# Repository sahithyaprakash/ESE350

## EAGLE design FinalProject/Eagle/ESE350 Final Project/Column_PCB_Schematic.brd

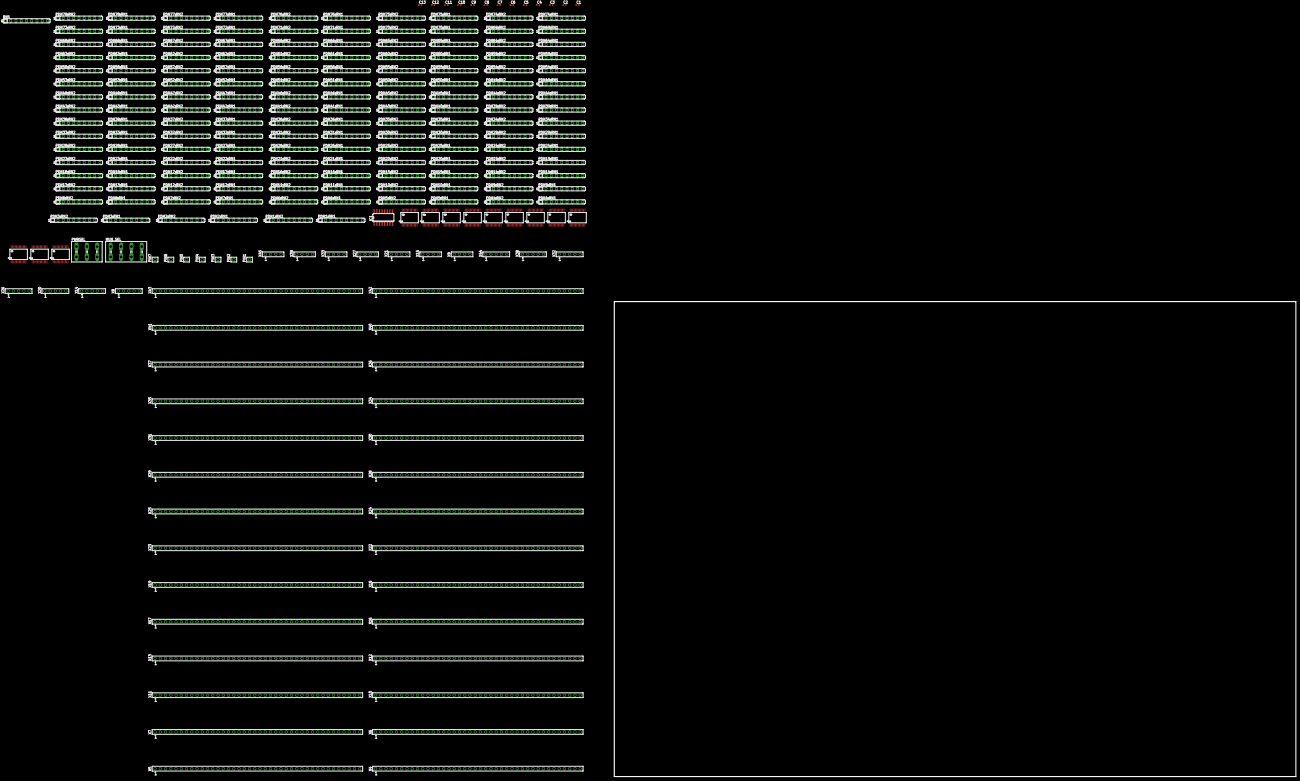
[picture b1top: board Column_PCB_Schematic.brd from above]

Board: 2 copper layers, 329.9 x 229.9 mm, 234 parts (0 on the bottom side), 1229 nets, no tracks yet.

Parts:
C1, C2, C3, C4, C5, C6, C7, C8, C9, C10, C11, C12, C13: 0.1uF; C0402
IC1: 74AC11238D; SO16
MUX_SEL: SH5-4
PDN1:RN1, PDN1:RN2, PDN2:RN1, PDN2:RN2, PDN3:RN1, PDN3:RN2, PDN4:RN1, PDN4:RN2, PDN5:RN1, PDN5:RN2, PDN6:RN1, PDN6:RN2, PDN7:RN1, PDN7:RN2, PDN8:RN1, PDN8:RN2, PDN9:RN1, PDN9:RN2, PDN10:RN1, PDN10:RN2, PDN11:RN1, PDN11:RN2, PDN12:RN1, PDN12:RN2, PDN13:RN1, PDN13:RN2, PDN14:RN1, PDN14:RN2, PDN15:RN1, PDN15:RN2, PDN16:RN1, PDN16:RN2, PDN17:RN1, PDN17:RN2, PDN18:RN1, PDN18:RN2, PDN19:RN1, PDN19:RN2, PDN20:RN1, PDN20:RN2, PDN21:RN1, PDN21:RN2, PDN22:RN1, PDN22:RN2, PDN23:RN1, PDN23:RN2, PDN24:RN1, PDN24:RN2, PDN25:RN1, PDN25:RN2, PDN26:RN1, PDN26:RN2, PDN27:RN1, PDN27:RN2, PDN28:RN1, PDN28:RN2, PDN29:RN1, PDN29:RN2, PDN30:RN1, PDN30:RN2, PDN31:RN1, PDN31:RN2, PDN32:RN1, PDN32:RN2, PDN33:RN1, PDN33:RN2, PDN34:RN1, PDN34:RN2, PDN35:RN1, PDN35:RN2, PDN36:RN1, PDN36:RN2, PDN37:RN1, PDN37:RN2, PDN38:RN1, PDN38:RN2, PDN39:RN1, PDN39:RN2, PDN40:RN1, PDN40:RN2, PDN41:RN1, PDN41:RN2, PDN42:RN1, PDN42:RN2, PDN43:RN1, PDN43:RN2, PDN44:RN1, PDN44:RN2, PDN45:RN1, PDN45:RN2, PDN46:RN1, PDN46:RN2, PDN47:RN1, PDN47:RN2, PDN48:RN1, PDN48:RN2, PDN49:RN1, PDN49:RN2, PDN50:RN1, PDN50:RN2, PDN51:RN1, PDN51:RN2, PDN52:RN1, PDN52:RN2, PDN53:RN1, PDN53:RN2, PDN54:RN1, PDN54:RN2, PDN55:RN1, PDN55:RN2, PDN56:RN1, PDN56:RN2, PDN57:RN1, PDN57:RN2, PDN58:RN1, PDN58:RN2, PDN59:RN1, PDN59:RN2, PDN60:RN1, PDN60:RN2, PDN61:RN1, PDN61:RN2, PDN62:RN1, PDN62:RN2, PDN63:RN1, PDN63:RN2, PDN64:RN1, PDN64:RN2, PDN65:RN1, PDN65:RN2, PDN66:RN1, PDN66:RN2, PDN67:RN1, PDN67:RN2, PDN68:RN1, PDN68:RN2, PDN69:RN1, PDN69:RN2, PDN70:RN1, PDN70:RN2, PDN71:RN1, PDN71:RN2, PDN72:RN1, PDN72:RN2, PDN73:RN1, PDN73:RN2, PDN74:RN1, PDN74:RN2, PDN75:RN1, PDN75:RN2, PDN76:RN1, PDN76:RN2, PDN77:RN1, PDN77:RN2, PDN78:RN1, PDN78:RN2: 560K; SIL9
PIN1, PIN2, PIN3, PIN4, PIN5, PIN6, PIN7: SSW-101-02-S-S
PWRSEL: SH5-3
RN1: 560K; SIL9
U$1, U$2, U$3, U$4, U$5, U$6, U$7, U$8, U$9, U$10, U$11, U$12: MUX-74HC4067SMD; SSOP24
X4, X5, X6, X7, X10, X11, X12, X13, X16, X17, X18, X19, X22, X23, X24, X25, X28, X29, X30, X31, X34, X35, X36, X37, X40, X41, X42, X43: SSW-140-02-S-S
X8, X14, X20, X26, X32, X38, X44: SSW-105-02-S-S
X9, X15, X21, X27, X33, X39, X45: SSW-104-02-S-S

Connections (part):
GND: IC1.4, IC1.9, IC1.10, PDN1:RN1.1, PDN1:RN2.1, PDN2:RN1.1, PDN2:RN2.1, PDN3:RN1.1, PDN3:RN2.1, PDN4:RN1.1, PDN4:RN2.1, PDN5:RN1.1, PDN5:RN2.1, PDN6:RN1.1, PDN6:RN2.1, PDN7:RN1.1, PDN7:RN2.1, PDN8:RN1.1, PDN8:RN2.1, PDN9:RN1.1, PDN9:RN2.1, PDN10:RN1.1, PDN10:RN2.1, PDN11:RN1.1, PDN11:RN2.1, PDN12:RN1.1, PDN12:RN2.1, PDN13:RN1.1, PDN13:RN2.1, PDN14:RN1.1, PDN14:RN2.1, PDN15:RN1.1, PDN15:RN2.1, PDN16:RN1.1, PDN16:RN2.1, PDN17:RN1.1, PDN17:RN2.1, PDN18:RN1.1, PDN18:RN2.1, PDN19:RN1.1, PDN19:RN2.1, PDN20:RN1.1, PDN20:RN2.1, PDN21:RN1.1, PDN21:RN2.1, PDN22:RN1.1, PDN22:RN2.1, PDN23:RN1.1, PDN23:RN2.1, PDN24:RN1.1, PDN24:RN2.1, PDN25:RN1.1, PDN25:RN2.1, PDN26:RN1.1, PDN26:RN2.1, PDN27:RN1.1, PDN27:RN2.1, PDN28:RN1.1, PDN28:RN2.1, PDN29:RN1.1, PDN29:RN2.1, PDN30:RN1.1, PDN30:RN2.1, PDN31:RN1.1, PDN31:RN2.1, PDN32:RN1.1, PDN32:RN2.1, PDN33:RN1.1, PDN33:RN2.1, PDN34:RN1.1, PDN34:RN2.1, PDN35:RN1.1, PDN35:RN2.1, PDN36:RN1.1, PDN36:RN2.1, PDN37:RN1.1, PDN37:RN2.1, PDN38:RN1.1, PDN38:RN2.1, PDN39:RN1.1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
L1S0: MUX_SEL.8, U$1.10, U$2.10, U$3.10, U$4.10, U$5.10, U$6.10, U$7.10, U$8.10, U$9.10, U$10.10, U$11.10
L1S1: MUX_SEL.7, U$1.11, U$2.11, U$3.11, U$4.11, U$5.11, U$6.11, U$7.11, U$8.11, U$9.11, U$10.11, U$11.11
L1S2: MUX_SEL.6, U$1.14, U$2.14, U$3.14, U$4.14, U$5.14, U$6.14, U$7.14, U$8.14, U$9.14, U$10.14, U$11.14
L1S3: MUX_SEL.5, U$1.13, U$2.13, U$3.13, U$4.13, U$5.13, U$6.13, U$7.13, U$8.13, U$9.13, U$10.13, U$11.13
L2S0: MUX_SEL.4, U$12.10
L2S1: MUX_SEL.3, U$12.11
L2S2: MUX_SEL.2, U$12.14
L2S3: MUX_SEL.1, U$12.13
unnamed: PDN78:RN2.7, U$11.1
unnamed: PDN78:RN2.8, U$2.1
unnamed: PDN78:RN2.9, U$6.1
unnamed: PDN78:RN1.2, U$5.1
unnamed: PDN78:RN1.3, U$4.1
unnamed: PDN78:RN1.4, U$3.1
unnamed: PDN78:RN1.6, U$7.1
unnamed: PDN78:RN1.7, U$8.1
unnamed: PDN78:RN1.8, U$9.1
unnamed: PDN78:RN1.9, U$10.1
unnamed: PDN1:RN1.9, X4.1
unnamed: PDN1:RN1.7, X4.2
unnamed: PDN1:RN1.5, X4.3
unnamed: PDN1:RN1.3, X4.4
unnamed: PDN1:RN2.9, X4.5
unnamed: PDN1:RN2.7, X4.6
unnamed: PDN1:RN2.5, X4.7
unnamed: PDN1:RN2.3, X4.8
unnamed: PDN2:RN1.9, X4.9
unnamed: PDN2:RN1.7, X4.10
unnamed: PDN2:RN1.5, X4.11
unnamed: PDN2:RN1.3, X4.12
unnamed: PDN2:RN2.9, X4.13
unnamed: PDN2:RN2.7, X4.14
unnamed: PDN2:RN2.5, X4.15
unnamed: PDN2:RN2.3, X4.16
unnamed: PDN3:RN1.9, X4.17
unnamed: PDN3:RN1.7, X4.18
unnamed: PDN3:RN1.5, X4.19
unnamed: PDN3:RN1.3, X4.20
unnamed: PDN3:RN2.9, X4.21
unnamed: PDN3:RN2.7, X4.22
unnamed: PDN3:RN2.5, X4.23
unnamed: PDN3:RN2.3, X4.24
unnamed: PDN4:RN1.9, X4.25
unnamed: PDN4:RN1.7, X4.26
unnamed: PDN4:RN1.5, X4.27
unnamed: PDN4:RN1.3, X4.28
unnamed: PDN4:RN2.9, X4.29
unnamed: PDN4:RN2.7, X4.30
unnamed: PDN4:RN2.5, X4.31
unnamed: PDN4:RN2.3, X4.32
unnamed: PDN5:RN1.9, X4.33
unnamed: PDN5:RN1.7, X4.34
unnamed: PDN5:RN1.5, X4.35
unnamed: PDN5:RN1.3, X4.36
unnamed: PDN5:RN2.9, X4.37
unnamed: PDN5:RN2.7, X4.38
unnamed: PDN5:RN2.5, X4.39
unnamed: PDN5:RN2.3, X4.40
unnamed: PDN6:RN1.9, X6.1
unnamed: PDN6:RN1.7, X6.2
unnamed: PDN6:RN1.5, X6.3
unnamed: PDN6:RN1.3, X6.4
unnamed: PDN6:RN2.9, X6.5
unnamed: PDN6:RN2.7, X6.6
unnamed: PDN6:RN2.5, X6.7
unnamed: PDN6:RN2.3, X6.8
unnamed: PDN7:RN1.9, X6.9
unnamed: PDN7:RN1.7, X6.10
unnamed: PDN7:RN1.5, X6.11
unnamed: PDN7:RN1.3, X6.12
unnamed: PDN7:RN2.9, X6.13
unnamed: PDN7:RN2.7, X6.14
unnamed: PDN7:RN2.5, X6.15
unnamed: PDN7:RN2.3, X6.16
unnamed: PDN8:RN1.9, X6.17
unnamed: PDN8:RN1.7, X6.18
unnamed: PDN8:RN1.5, X6.19
unnamed: PDN8:RN1.3, X6.20
unnamed: PDN8:RN2.9, X6.21
unnamed: PDN8:RN2.7, X6.22
unnamed: PDN8:RN2.5, X6.23
unnamed: PDN8:RN2.3, X6.24
unnamed: PDN9:RN1.9, X6.25
unnamed: PDN9:RN1.7, X6.26
unnamed: PDN9:RN1.5, X6.27
unnamed: PDN9:RN1.3, X6.28
unnamed: PDN9:RN2.9, X6.29
unnamed: PDN9:RN2.7, X6.30
unnamed: PDN9:RN2.5, X6.31
unnamed: PDN9:RN2.3, X6.32
unnamed: PDN10:RN1.9, X6.33
unnamed: PDN10:RN1.7, X6.34
unnamed: PDN10:RN1.5, X6.35
unnamed: PDN10:RN1.3, X6.36
unnamed: PDN10:RN2.9, X6.37
unnamed: PDN10:RN2.7, X6.38
unnamed: PDN10:RN2.5, X6.39
unnamed: PDN10:RN2.3, X6.40
unnamed: PDN11:RN1.9, X8.1
unnamed: PDN11:RN1.7, X8.2
unnamed: PDN11:RN1.5, X8.3
unnamed: PDN11:RN1.3, X8.4
unnamed: PDN11:RN2.9, X8.5
unnamed: PDN12:RN1.9, X10.1
unnamed: PDN12:RN1.7, X10.2
unnamed: PDN12:RN1.5, X10.3
unnamed: PDN12:RN1.3, X10.4
unnamed: PDN12:RN2.9, X10.5
unnamed: PDN12:RN2.7, X10.6
unnamed: PDN12:RN2.5, X10.7
unnamed: PDN12:RN2.3, X10.8
unnamed: PDN13:RN1.9, X10.9
unnamed: PDN13:RN1.7, X10.10
unnamed: PDN13:RN1.5, X10.11
unnamed: PDN13:RN1.3, X10.12
unnamed: PDN13:RN2.9, X10.13
unnamed: PDN13:RN2.7, X10.14
unnamed: PDN13:RN2.5, X10.15
unnamed: PDN13:RN2.3, X10.16
unnamed: PDN78:RN1.5, U$1.1
unnamed: PDN14:RN1.9, X10.17
unnamed: PDN14:RN1.7, X10.18
unnamed: PDN14:RN1.5, X10.19
unnamed: PDN14:RN1.3, X10.20
unnamed: PDN14:RN2.9, X10.21
unnamed: PDN14:RN2.7, X10.22
unnamed: PDN14:RN2.5, X10.23
unnamed: PDN14:RN2.3, X10.24
unnamed: PDN15:RN1.9, X10.25
unnamed: PDN15:RN1.7, X10.26
unnamed: PDN15:RN1.5, X10.27
unnamed: PDN15:RN1.3, X10.28
unnamed: PDN15:RN2.9, X10.29
unnamed: PDN15:RN2.7, X10.30
unnamed: PDN15:RN2.5, X10.31
unnamed: PDN15:RN2.3, X10.32
unnamed: PDN16:RN1.9, X10.33
unnamed: PDN16:RN1.7, X10.34
unnamed: PDN16:RN1.5, X10.35
unnamed: PDN16:RN1.3, X10.36
unnamed: PDN16:RN2.9, X10.37
unnamed: PDN16:RN2.7, X10.38
unnamed: PDN16:RN2.5, X10.39
unnamed: PDN16:RN2.3, X10.40
unnamed: PDN17:RN1.9, X12.1
unnamed: PDN17:RN1.7, X12.2
unnamed: PDN17:RN1.5, X12.3
unnamed: PDN17:RN1.3, X12.4
unnamed: PDN17:RN2.9, X12.5
unnamed: PDN17:RN2.7, X12.6
unnamed: PDN17:RN2.5, X12.7
unnamed: PDN17:RN2.3, X12.8
unnamed: PDN18:RN1.9, X12.9
unnamed: PDN18:RN1.7, X12.10
unnamed: PDN18:RN1.5, X12.11
unnamed: PDN18:RN1.3, X12.12
unnamed: PDN18:RN2.9, X12.13
unnamed: PDN18:RN2.7, X12.14
unnamed: PDN18:RN2.5, X12.15
unnamed: PDN18:RN2.3, X12.16
unnamed: PDN19:RN1.9, X12.17
unnamed: PDN19:RN1.7, X12.18
unnamed: PDN19:RN1.5, X12.19
unnamed: PDN19:RN1.3, X12.20
unnamed: PDN19:RN2.9, X12.21
unnamed: PDN19:RN2.7, X12.22
unnamed: PDN19:RN2.5, X12.23
unnamed: PDN19:RN2.3, X12.24
unnamed: PDN20:RN1.9, X12.25
unnamed: PDN20:RN1.7, X12.26
unnamed: PDN20:RN1.5, X12.27
unnamed: PDN20:RN1.3, X12.28
unnamed: PDN20:RN2.9, X12.29
unnamed: PDN20:RN2.7, X12.30
unnamed: PDN20:RN2.5, X12.31
unnamed: PDN20:RN2.3, X12.32
unnamed: PDN21:RN1.9, X12.33
unnamed: PDN21:RN1.7, X12.34
unnamed: PDN21:RN1.5, X12.35
unnamed: PDN21:RN1.3, X12.36
unnamed: PDN21:RN2.9, X12.37
unnamed: PDN21:RN2.7, X12.38
unnamed: PDN21:RN2.5, X12.39
unnamed: PDN21:RN2.3, X12.40
unnamed: PDN22:RN1.9, X14.1
unnamed: PDN22:RN1.7, X14.2
unnamed: PDN22:RN1.5, X14.3
unnamed: PDN22:RN1.3, X14.4
unnamed: PDN22:RN2.9, X14.5
unnamed: PDN23:RN1.9, X16.1
unnamed: PDN23:RN1.7, X16.2
unnamed: PDN23:RN1.5, X16.3
unnamed: PDN23:RN1.3, X16.4
unnamed: PDN23:RN2.9, X16.5
unnamed: PDN23:RN2.7, X16.6
unnamed: PDN23:RN2.5, X16.7
unnamed: PDN23:RN2.3, X16.8
unnamed: PDN24:RN1.9, X16.9
unnamed: PDN24:RN1.7, X16.10
unnamed: PDN24:RN1.5, X16.11
unnamed: PDN24:RN1.3, X16.12
unnamed: PDN24:RN2.9, X16.13
unnamed: PDN24:RN2.7, X16.14
unnamed: PDN24:RN2.5, X16.15
unnamed: PDN24:RN2.3, X16.16
unnamed: PDN25:RN1.9, X16.17
unnamed: PDN25:RN1.7, X16.18
unnamed: PDN25:RN1.5, X16.19
unnamed: PDN25:RN1.3, X16.20
unnamed: PDN25:RN2.9, X16.21
unnamed: PDN25:RN2.7, X16.22
unnamed: PDN25:RN2.5, X16.23
unnamed: PDN25:RN2.3, X16.24
unnamed: PDN26:RN1.9, X16.25
unnamed: PDN26:RN1.7, X16.26
unnamed: PDN26:RN1.5, X16.27
unnamed: PDN26:RN1.3, X16.28
unnamed: PDN26:RN2.9, X16.29
unnamed: PDN26:RN2.7, X16.30
unnamed: PDN26:RN2.5, X16.31
unnamed: PDN26:RN2.3, X16.32
unnamed: PDN27:RN1.9, X16.33
unnamed: PDN27:RN1.7, X16.34
unnamed: PDN27:RN1.5, X16.35
unnamed: PDN27:RN1.3, X16.36
unnamed: PDN27:RN2.9, X16.37
unnamed: PDN27:RN2.7, X16.38
unnamed: PDN27:RN2.5, X16.39
unnamed: PDN27:RN2.3, X16.40
unnamed: PDN28:RN1.9, X18.1
unnamed: PDN28:RN1.7, X18.2
unnamed: PDN28:RN1.5, X18.3
unnamed: PDN28:RN1.3, X18.4
unnamed: PDN28:RN2.9, X18.5
unnamed: PDN28:RN2.7, X18.6
unnamed: PDN28:RN2.5, X18.7
unnamed: PDN28:RN2.3, X18.8
unnamed: PDN29:RN1.9, X18.9
unnamed: PDN29:RN1.7, X18.10
unnamed: PDN29:RN1.5, X18.11
unnamed: PDN29:RN1.3, X18.12
unnamed: PDN29:RN2.9, X18.13
unnamed: PDN29:RN2.7, X18.14
unnamed: PDN29:RN2.5, X18.15
unnamed: PDN29:RN2.3, X18.16
unnamed: PDN30:RN1.9, X18.17
unnamed: PDN30:RN1.7, X18.18
unnamed: PDN30:RN1.5, X18.19
unnamed: PDN30:RN1.3, X18.20
unnamed: PDN30:RN2.9, X18.21
unnamed: PDN30:RN2.7, X18.22
unnamed: PDN30:RN2.5, X18.23
unnamed: PDN30:RN2.3, X18.24
unnamed: PDN31:RN1.9, X18.25
unnamed: PDN31:RN1.7, X18.26
unnamed: PDN31:RN1.5, X18.27
unnamed: PDN31:RN1.3, X18.28
unnamed: PDN31:RN2.9, X18.29
unnamed: PDN31:RN2.7, X18.30
unnamed: PDN31:RN2.5, X18.31
unnamed: PDN31:RN2.3, X18.32
unnamed: PDN32:RN1.9, X18.33
unnamed: PDN32:RN1.7, X18.34
unnamed: PDN32:RN1.5, X18.35
unnamed: PDN32:RN1.3, X18.36
unnamed: PDN32:RN2.9, X18.37
unnamed: PDN32:RN2.7, X18.38
unnamed: PDN32:RN2.5, X18.39
unnamed: PDN32:RN2.3, X18.40
unnamed: PDN33:RN1.9, X20.1
unnamed: PDN33:RN1.7, X20.2
unnamed: PDN33:RN1.5, X20.3
unnamed: PDN33:RN1.3, X20.4
unnamed: PDN33:RN2.9, X20.5
unnamed: PDN34:RN1.9, X22.1
unnamed: PDN34:RN1.7, X22.2
unnamed: PDN34:RN1.5, X22.3
unnamed: PDN34:RN1.3, X22.4
unnamed: PDN34:RN2.9, X22.5
unnamed: PDN34:RN2.7, X22.6
unnamed: PDN34:RN2.5, X22.7
unnamed: PDN34:RN2.3, X22.8
unnamed: PDN35:RN1.9, X22.9
unnamed: PDN35:RN1.7, X22.10
unnamed: PDN35:RN1.5, X22.11
unnamed: PDN35:RN1.3, X22.12
unnamed: PDN35:RN2.9, X22.13
unnamed: PDN35:RN2.7, X22.14
unnamed: PDN35:RN2.5, X22.15
unnamed: PDN35:RN2.3, X22.16
unnamed: PDN36:RN1.9, X22.17
unnamed: PDN36:RN1.7, X22.18
unnamed: PDN36:RN1.5, X22.19
unnamed: PDN36:RN1.3, X22.20
unnamed: PDN36:RN2.9, X22.21
unnamed: PDN36:RN2.7, X22.22
unnamed: PDN36:RN2.5, X22.23
unnamed: PDN36:RN2.3, X22.24
unnamed: PDN37:RN1.9, X22.25
unnamed: PDN37:RN1.7, X22.26
unnamed: PDN37:RN1.5, X22.27
unnamed: PDN37:RN1.3, X22.28
unnamed: PDN37:RN2.9, X22.29
unnamed: PDN37:RN2.7, X22.30
unnamed: PDN37:RN2.5, X22.31
unnamed: PDN37:RN2.3, X22.32
unnamed: PDN38:RN1.9, X22.33
unnamed: PDN38:RN1.7, X22.34
unnamed: PDN38:RN1.5, X22.35
unnamed: PDN38:RN1.3, X22.36
unnamed: PDN38:RN2.9, X22.37
unnamed: PDN38:RN2.7, X22.38
unnamed: PDN38:RN2.5, X22.39
unnamed: PDN38:RN2.3, X22.40
unnamed: PDN39:RN1.9, X24.1
unnamed: PDN39:RN1.7, X24.2
unnamed: PDN39:RN1.5, X24.3
unnamed: PDN39:RN1.3, X24.4
unnamed: PDN39:RN2.9, X24.5
unnamed: PDN39:RN2.7, X24.6
unnamed: PDN39:RN2.5, X24.7
unnamed: PDN39:RN2.3, X24.8
unnamed: PDN40:RN1.9, X24.9
unnamed: PDN40:RN1.7, X24.10
unnamed: PDN40:RN1.5, X24.11
unnamed: PDN40:RN1.3, X24.12
unnamed: PDN40:RN2.9, X24.13
unnamed: PDN40:RN2.7, X24.14
unnamed: PDN40:RN2.5, X24.15
unnamed: PDN40:RN2.3, X24.16
unnamed: PDN41:RN1.9, X24.17
unnamed: PDN41:RN1.7, X24.18
unnamed: PDN41:RN1.5, X24.19
unnamed: PDN41:RN1.3, X24.20
unnamed: PDN41:RN2.9, X24.21
unnamed: PDN41:RN2.7, X24.22
unnamed: PDN41:RN2.5, X24.23
unnamed: PDN41:RN2.3, X24.24
unnamed: PDN42:RN1.9, X24.25
unnamed: PDN42:RN1.7, X24.26
unnamed: PDN42:RN1.5, X24.27
unnamed: PDN42:RN1.3, X24.28
unnamed: PDN42:RN2.9, X24.29
unnamed: PDN42:RN2.7, X24.30
unnamed: PDN42:RN2.5, X24.31
unnamed: PDN42:RN2.3, X24.32
unnamed: PDN43:RN1.9, X24.33
unnamed: PDN43:RN1.7, X24.34
unnamed: PDN43:RN1.5, X24.35
unnamed: PDN43:RN1.3, X24.36
unnamed: PDN43:RN2.9, X24.37
unnamed: PDN43:RN2.7, X24.38
unnamed: PDN43:RN2.5, X24.39
unnamed: PDN43:RN2.3, X24.40
unnamed: PDN44:RN1.9, X26.1
unnamed: PDN44:RN1.7, X26.2
unnamed: PDN44:RN1.5, X26.3
unnamed: PDN44:RN1.3, X26.4
unnamed: PDN44:RN2.9, X26.5
unnamed: PDN45:RN1.9, X28.1
unnamed: PDN45:RN1.7, X28.2
unnamed: PDN45:RN1.5, X28.3
unnamed: PDN45:RN1.3, X28.4
unnamed: PDN45:RN2.9, X28.5
unnamed: PDN45:RN2.7, X28.6
unnamed: PDN45:RN2.5, X28.7
unnamed: PDN45:RN2.3, X28.8
unnamed: PDN46:RN1.9, X28.9
unnamed: PDN46:RN1.7, X28.10
unnamed: PDN46:RN1.5, X28.11
unnamed: PDN46:RN1.3, X28.12
unnamed: PDN46:RN2.9, X28.13
unnamed: PDN46:RN2.7, X28.14
unnamed: PDN46:RN2.5, X28.15
unnamed: PDN46:RN2.3, X28.16
unnamed: PDN47:RN1.9, X28.17
unnamed: PDN47:RN1.7, X28.18
unnamed: PDN47:RN1.5, X28.19
unnamed: PDN47:RN1.3, X28.20
unnamed: PDN47:RN2.9, X28.21
unnamed: PDN47:RN2.7, X28.22
unnamed: PDN47:RN2.5, X28.23
unnamed: PDN47:RN2.3, X28.24
unnamed: PDN48:RN1.9, X28.25
unnamed: PDN48:RN1.7, X28.26
unnamed: PDN48:RN1.5, X28.27
unnamed: PDN48:RN1.3, X28.28
unnamed: PDN48:RN2.9, X28.29
unnamed: PDN48:RN2.7, X28.30
unnamed: PDN48:RN2.5, X28.31
unnamed: PDN48:RN2.3, X28.32
unnamed: PDN49:RN1.9, X28.33
unnamed: PDN49:RN1.7, X28.34
unnamed: PDN49:RN1.5, X28.35
unnamed: PDN49:RN1.3, X28.36
unnamed: PDN49:RN2.9, X28.37
unnamed: PDN49:RN2.7, X28.38
unnamed: PDN49:RN2.5, X28.39
unnamed: PDN49:RN2.3, X28.40
unnamed: PDN50:RN1.9, X30.1
unnamed: PDN50:RN1.7, X30.2
unnamed: PDN50:RN1.5, X30.3
unnamed: PDN50:RN1.3, X30.4
unnamed: PDN50:RN2.9, X30.5
unnamed: PDN50:RN2.7, X30.6
unnamed: PDN50:RN2.5, X30.7
unnamed: PDN50:RN2.3, X30.8
unnamed: PDN51:RN1.9, X30.9
unnamed: PDN51:RN1.7, X30.10
unnamed: PDN51:RN1.5, X30.11
unnamed: PDN51:RN1.3, X30.12
unnamed: PDN51:RN2.9, X30.13
unnamed: PDN51:RN2.7, X30.14
unnamed: PDN51:RN2.5, X30.15
unnamed: PDN51:RN2.3, X30.16
unnamed: PDN52:RN1.9, X30.17
unnamed: PDN52:RN1.7, X30.18
unnamed: PDN52:RN1.5, X30.19
unnamed: PDN52:RN1.3, X30.20
unnamed: PDN52:RN2.9, X30.21
unnamed: PDN52:RN2.7, X30.22
unnamed: PDN52:RN2.5, X30.23
unnamed: PDN52:RN2.3, X30.24
unnamed: PDN53:RN1.9, X30.25
unnamed: PDN53:RN1.7, X30.26
unnamed: PDN53:RN1.5, X30.27
unnamed: PDN53:RN1.3, X30.28
unnamed: PDN53:RN2.9, X30.29
unnamed: PDN53:RN2.7, X30.30
unnamed: PDN53:RN2.5, X30.31
unnamed: PDN53:RN2.3, X30.32
unnamed: PDN54:RN1.9, X30.33
unnamed: PDN54:RN1.7, X30.34
unnamed: PDN54:RN1.5, X30.35
unnamed: PDN54:RN1.3, X30.36
unnamed: PDN54:RN2.9, X30.37
unnamed: PDN54:RN2.7, X30.38
unnamed: PDN54:RN2.5, X30.39
unnamed: PDN54:RN2.3, X30.40
unnamed: PDN55:RN1.9, X32.1
unnamed: PDN55:RN1.7, X32.2
unnamed: PDN55:RN1.5, X32.3
unnamed: PDN55:RN1.3, X32.4
unnamed: PDN55:RN2.9, X32.5
unnamed: PDN56:RN1.9, X34.1
unnamed: PDN56:RN1.7, X34.2
unnamed: PDN56:RN1.5, X34.3
unnamed: PDN56:RN1.3, X34.4
unnamed: PDN56:RN2.9, X34.5
unnamed: PDN56:RN2.7, X34.6
unnamed: PDN56:RN2.5, X34.7
unnamed: PDN56:RN2.3, X34.8
unnamed: PDN57:RN1.9, X34.9
unnamed: PDN57:RN1.7, X34.10
unnamed: PDN57:RN1.5, X34.11
unnamed: PDN57:RN1.3, X34.12
unnamed: PDN57:RN2.9, X34.13
unnamed: PDN57:RN2.7, X34.14
unnamed: PDN57:RN2.5, X34.15
unnamed: PDN57:RN2.3, X34.16
unnamed: PDN58:RN1.9, X34.17
unnamed: PDN58:RN1.7, X34.18
unnamed: PDN58:RN1.5, X34.19
unnamed: PDN58:RN1.3, X34.20
unnamed: PDN58:RN2.9, X34.21
unnamed: PDN58:RN2.7, X34.22
unnamed: PDN58:RN2.5, X34.23
unnamed: PDN58:RN2.3, X34.24
unnamed: PDN59:RN1.9, X34.25
unnamed: PDN59:RN1.7, X34.26
unnamed: PDN59:RN1.5, X34.27
unnamed: PDN59:RN1.3, X34.28
unnamed: PDN59:RN2.9, X34.29
unnamed: PDN59:RN2.7, X34.30
unnamed: PDN59:RN2.5, X34.31
unnamed: PDN59:RN2.3, X34.32
unnamed: PDN60:RN1.9, X34.33
unnamed: PDN60:RN1.7, X34.34
unnamed: PDN60:RN1.5, X34.35
unnamed: PDN60:RN1.3, X34.36
unnamed: PDN60:RN2.9, X34.37
unnamed: PDN60:RN2.7, X34.38
unnamed: PDN60:RN2.5, X34.39
unnamed: PDN60:RN2.3, X34.40
unnamed: PDN61:RN1.9, X36.1
unnamed: PDN61:RN1.7, X36.2
unnamed: PDN61:RN1.5, X36.3
unnamed: PDN61:RN1.3, X36.4
unnamed: PDN61:RN2.9, X36.5
unnamed: PDN61:RN2.7, X36.6
unnamed: PDN61:RN2.5, X36.7
unnamed: PDN61:RN2.3, X36.8
unnamed: PDN62:RN1.9, X36.9
unnamed: PDN62:RN1.7, X36.10
unnamed: PDN62:RN1.5, X36.11
unnamed: PDN62:RN1.3, X36.12
unnamed: PDN62:RN2.9, X36.13
unnamed: PDN62:RN2.7, X36.14
unnamed: PDN62:RN2.5, X36.15
unnamed: PDN62:RN2.3, X36.16
unnamed: PDN63:RN1.9, X36.17
unnamed: PDN63:RN1.7, X36.18
unnamed: PDN63:RN1.5, X36.19
unnamed: PDN63:RN1.3, X36.20
unnamed: PDN63:RN2.9, X36.21
unnamed: PDN63:RN2.7, X36.22
unnamed: PDN63:RN2.5, X36.23
unnamed: PDN63:RN2.3, X36.24
unnamed: PDN64:RN1.9, X36.25
unnamed: PDN64:RN1.7, X36.26
unnamed: PDN64:RN1.5, X36.27
unnamed: PDN64:RN1.3, X36.28
unnamed: PDN64:RN2.9, X36.29
unnamed: PDN64:RN2.7, X36.30
unnamed: PDN64:RN2.5, X36.31
unnamed: PDN64:RN2.3, X36.32
unnamed: PDN65:RN1.9, X36.33
unnamed: PDN65:RN1.7, X36.34
unnamed: PDN65:RN1.5, X36.35
unnamed: PDN65:RN1.3, X36.36
unnamed: PDN65:RN2.9, X36.37
unnamed: PDN65:RN2.7, X36.38
unnamed: PDN65:RN2.5, X36.39
unnamed: PDN65:RN2.3, X36.40
unnamed: PDN66:RN1.9, X38.1
unnamed: PDN66:RN1.7, X38.2
unnamed: PDN66:RN1.5, X38.3
unnamed: PDN66:RN1.3, X38.4
unnamed: PDN66:RN2.9, X38.5
unnamed: PDN67:RN1.9, X40.1
unnamed: PDN67:RN1.7, X40.2
unnamed: PDN67:RN1.5, X40.3
unnamed: PDN67:RN1.3, X40.4
unnamed: PDN67:RN2.9, X40.5
unnamed: PDN67:RN2.7, X40.6
unnamed: PDN67:RN2.5, X40.7
unnamed: PDN67:RN2.3, X40.8
unnamed: PDN68:RN1.9, X40.9
unnamed: PDN68:RN1.7, X40.10
unnamed: PDN68:RN1.5, X40.11
unnamed: PDN68:RN1.3, X40.12
unnamed: PDN68:RN2.9, X40.13
unnamed: PDN68:RN2.7, X40.14
unnamed: PDN68:RN2.5, X40.15
unnamed: PDN68:RN2.3, X40.16
unnamed: PDN69:RN1.9, X40.17
unnamed: PDN69:RN1.7, X40.18
unnamed: PDN69:RN1.5, X40.19
unnamed: PDN69:RN1.3, X40.20
unnamed: PDN69:RN2.9, X40.21
unnamed: PDN69:RN2.7, X40.22
unnamed: PDN69:RN2.5, X40.23
unnamed: PDN69:RN2.3, X40.24
unnamed: PDN70:RN1.9, X40.25
unnamed: PDN70:RN1.7, X40.26
unnamed: PDN70:RN1.5, X40.27
unnamed: PDN70:RN1.3, X40.28
unnamed: PDN70:RN2.9, X40.29
unnamed: PDN70:RN2.7, X40.30
unnamed: PDN70:RN2.5, X40.31
unnamed: PDN70:RN2.3, X40.32
unnamed: PDN71:RN1.9, X40.33
unnamed: PDN71:RN1.7, X40.34
unnamed: PDN71:RN1.5, X40.35
unnamed: PDN71:RN1.3, X40.36
unnamed: PDN71:RN2.9, X40.37
unnamed: PDN71:RN2.7, X40.38
unnamed: PDN71:RN2.5, X40.39
unnamed: PDN71:RN2.3, X40.40
unnamed: PDN72:RN1.9, X42.1
unnamed: PDN72:RN1.7, X42.2
unnamed: PDN72:RN1.5, X42.3
unnamed: PDN72:RN1.3, X42.4
unnamed: PDN72:RN2.9, X42.5
unnamed: PDN72:RN2.7, X42.6
unnamed: PDN72:RN2.5, X42.7
unnamed: PDN72:RN2.3, X42.8
unnamed: PDN73:RN1.9, X42.9
unnamed: PDN73:RN1.7, X42.10
unnamed: PDN73:RN1.5, X42.11
unnamed: PDN73:RN1.3, X42.12
unnamed: PDN73:RN2.9, X42.13
unnamed: PDN73:RN2.7, X42.14
unnamed: PDN73:RN2.5, X42.15
unnamed: PDN73:RN2.3, X42.16
unnamed: PDN74:RN1.9, X42.17
unnamed: PDN74:RN1.7, X42.18
unnamed: PDN74:RN1.5, X42.19
unnamed: PDN74:RN1.3, X42.20
unnamed: PDN74:RN2.9, X42.21
unnamed: PDN74:RN2.7, X42.22
unnamed: PDN74:RN2.5, X42.23
unnamed: PDN74:RN2.3, X42.24
unnamed: PDN75:RN1.9, X42.25
unnamed: PDN75:RN1.7, X42.26
unnamed: PDN75:RN1.5, X42.27
unnamed: PDN75:RN1.3, X42.28
unnamed: PDN75:RN2.9, X42.29
unnamed: PDN75:RN2.7, X42.30
unnamed: PDN75:RN2.5, X42.31
unnamed: PDN75:RN2.3, X42.32
unnamed: PDN76:RN1.9, X42.33
unnamed: PDN76:RN1.7, X42.34
unnamed: PDN76:RN1.5, X42.35
unnamed: PDN76:RN1.3, X42.36
unnamed: PDN76:RN2.9, X42.37
unnamed: PDN76:RN2.7, X42.38
unnamed: PDN76:RN2.5, X42.39
unnamed: PDN76:RN2.3, X42.40
unnamed: PDN77:RN1.9, X44.1
unnamed: PDN77:RN1.7, X44.2
unnamed: PDN77:RN1.5, X44.3
unnamed: PDN77:RN1.3, X44.4
unnamed: PDN77:RN2.9, X44.5
unnamed: PDN1:RN1.8, X5.1
unnamed: PDN1:RN1.6, X5.2
unnamed: PDN1:RN1.4, X5.3
unnamed: PDN1:RN1.2, X5.4
unnamed: PDN1:RN2.8, X5.5
unnamed: PDN1:RN2.6, X5.6
unnamed: PDN1:RN2.4, X5.7
unnamed: PDN1:RN2.2, X5.8
unnamed: PDN2:RN1.8, X5.9
unnamed: PDN2:RN1.6, X5.10
unnamed: PDN2:RN1.4, X5.11
unnamed: PDN2:RN1.2, X5.12
unnamed: PDN2:RN2.8, X5.13
unnamed: PDN2:RN2.6, X5.14
unnamed: PDN2:RN2.4, X5.15
unnamed: PDN2:RN2.2, X5.16
unnamed: PDN3:RN1.8, X5.17
unnamed: PDN3:RN1.6, X5.18
unnamed: PDN3:RN1.4, X5.19
unnamed: PDN3:RN1.2, X5.20
unnamed: PDN3:RN2.8, X5.21
unnamed: PDN3:RN2.6, X5.22
unnamed: PDN3:RN2.4, X5.23
unnamed: PDN3:RN2.2, X5.24
unnamed: PDN4:RN1.8, X5.25
unnamed: PDN4:RN1.6, X5.26
unnamed: PDN4:RN1.4, X5.27
unnamed: PDN4:RN1.2, X5.28
unnamed: PDN4:RN2.8, X5.29
unnamed: PDN4:RN2.6, X5.30
unnamed: PDN4:RN2.4, X5.31
unnamed: PDN4:RN2.2, X5.32
unnamed: PDN5:RN1.8, X5.33
unnamed: PDN5:RN1.6, X5.34
unnamed: PDN5:RN1.4, X5.35
unnamed: PDN5:RN1.2, X5.36
unnamed: PDN5:RN2.8, X5.37
unnamed: PDN5:RN2.6, X5.38
unnamed: PDN5:RN2.4, X5.39
unnamed: PDN5:RN2.2, X5.40
unnamed: PDN6:RN1.8, X7.1
unnamed: PDN6:RN1.6, X7.2
unnamed: PDN6:RN1.4, X7.3
unnamed: PDN6:RN1.2, X7.4
unnamed: PDN6:RN2.8, X7.5
unnamed: PDN6:RN2.6, X7.6
unnamed: PDN6:RN2.4, X7.7
unnamed: PDN6:RN2.2, X7.8
unnamed: PDN7:RN1.8, X7.9
unnamed: PDN7:RN1.6, X7.10
unnamed: PDN7:RN1.4, X7.11
unnamed: PDN7:RN1.2, X7.12
unnamed: PDN7:RN2.8, X7.13
unnamed: PDN7:RN2.6, X7.14
unnamed: PDN7:RN2.4, X7.15
unnamed: PDN7:RN2.2, X7.16
unnamed: PDN8:RN1.8, X7.17
unnamed: PDN8:RN1.6, X7.18
unnamed: PDN8:RN1.4, X7.19
unnamed: PDN8:RN1.2, X7.20
unnamed: PDN8:RN2.8, X7.21
unnamed: PDN8:RN2.6, X7.22
unnamed: PDN8:RN2.4, X7.23
unnamed: PDN8:RN2.2, X7.24
unnamed: PDN9:RN1.8, X7.25
unnamed: PDN9:RN1.6, X7.26
unnamed: PDN9:RN1.4, X7.27
unnamed: PDN9:RN1.2, X7.28
unnamed: PDN9:RN2.8, X7.29
unnamed: PDN9:RN2.6, X7.30
unnamed: PDN9:RN2.4, X7.31
unnamed: PDN9:RN2.2, X7.32
unnamed: PDN10:RN1.8, X7.33
unnamed: PDN10:RN1.6, X7.34
unnamed: PDN10:RN1.4, X7.35
unnamed: PDN10:RN1.2, X7.36
unnamed: PDN10:RN2.8, X7.37
unnamed: PDN10:RN2.6, X7.38
unnamed: PDN10:RN2.4, X7.39
unnamed: PDN10:RN2.2, X7.40
unnamed: PDN11:RN1.8, X9.1
unnamed: PDN11:RN1.6, X9.2
unnamed: PDN11:RN1.4, X9.3
unnamed: PDN11:RN1.2, X9.4
unnamed: PDN12:RN1.8, X11.1
unnamed: PDN12:RN1.6, X11.2
unnamed: PDN12:RN1.4, X11.3
unnamed: PDN12:RN1.2, X11.4
unnamed: PDN12:RN2.8, X11.5
unnamed: PDN12:RN2.6, X11.6
unnamed: PDN12:RN2.4, X11.7
unnamed: PDN12:RN2.2, X11.8
unnamed: PDN13:RN1.8, X11.9
unnamed: PDN13:RN1.6, X11.10
unnamed: PDN13:RN1.4, X11.11
unnamed: PDN13:RN1.2, X11.12
unnamed: PDN13:RN2.8, X11.13
unnamed: PDN13:RN2.6, X11.14
unnamed: PDN13:RN2.4, X11.15
unnamed: PDN13:RN2.2, X11.16
unnamed: PDN14:RN1.8, X11.17
unnamed: PDN14:RN1.6, X11.18
unnamed: PDN14:RN1.4, X11.19
unnamed: PDN14:RN1.2, X11.20
unnamed: PDN14:RN2.8, X11.21
unnamed: PDN14:RN2.6, X11.22
unnamed: PDN14:RN2.4, X11.23
unnamed: PDN14:RN2.2, X11.24
unnamed: PDN15:RN1.8, X11.25
unnamed: PDN15:RN1.6, X11.26
unnamed: PDN15:RN1.4, X11.27
unnamed: PDN15:RN1.2, X11.28
unnamed: PDN15:RN2.8, X11.29
unnamed: PDN15:RN2.6, X11.30
unnamed: PDN15:RN2.4, X11.31
unnamed: PDN15:RN2.2, X11.32
unnamed: PDN16:RN1.8, X11.33
unnamed: PDN16:RN1.6, X11.34
unnamed: PDN16:RN1.4, X11.35
unnamed: PDN16:RN1.2, X11.36
unnamed: PDN16:RN2.8, X11.37
unnamed: PDN16:RN2.6, X11.38
unnamed: PDN16:RN2.4, X11.39
unnamed: PDN16:RN2.2, X11.40
unnamed: PDN17:RN1.8, X13.1
unnamed: PDN17:RN1.6, X13.2
unnamed: PDN17:RN1.4, X13.3
unnamed: PDN17:RN1.2, X13.4
unnamed: PDN17:RN2.8, X13.5
unnamed: PDN17:RN2.6, X13.6
unnamed: PDN17:RN2.4, X13.7
unnamed: PDN17:RN2.2, X13.8
unnamed: PDN18:RN1.8, X13.9
unnamed: PDN18:RN1.6, X13.10
unnamed: PDN18:RN1.4, X13.11
unnamed: PDN18:RN1.2, X13.12
unnamed: PDN18:RN2.8, X13.13
unnamed: PDN18:RN2.6, X13.14
unnamed: PDN18:RN2.4, X13.15
unnamed: PDN18:RN2.2, X13.16
unnamed: PDN19:RN1.8, X13.17
unnamed: PDN19:RN1.6, X13.18
unnamed: PDN19:RN1.4, X13.19
unnamed: PDN19:RN1.2, X13.20
unnamed: PDN19:RN2.8, X13.21
unnamed: PDN19:RN2.6, X13.22
unnamed: PDN19:RN2.4, X13.23
unnamed: PDN19:RN2.2, X13.24
unnamed: PDN20:RN1.8, X13.25
unnamed: PDN20:RN1.6, X13.26
unnamed: PDN20:RN1.4, X13.27
unnamed: PDN20:RN1.2, X13.28
unnamed: PDN20:RN2.8, X13.29
unnamed: PDN20:RN2.6, X13.30
unnamed: PDN20:RN2.4, X13.31
unnamed: PDN20:RN2.2, X13.32
unnamed: PDN21:RN1.8, X13.33
unnamed: PDN21:RN1.6, X13.34
unnamed: PDN21:RN1.4, X13.35
unnamed: PDN21:RN1.2, X13.36
unnamed: PDN21:RN2.8, X13.37
unnamed: PDN21:RN2.6, X13.38
unnamed: PDN21:RN2.4, X13.39
unnamed: PDN21:RN2.2, X13.40
unnamed: PDN22:RN1.8, X15.1
unnamed: PDN22:RN1.6, X15.2
unnamed: PDN22:RN1.4, X15.3
unnamed: PDN22:RN1.2, X15.4
unnamed: PDN23:RN1.8, X17.1
unnamed: PDN23:RN1.6, X17.2
unnamed: PDN23:RN1.4, X17.3
unnamed: PDN23:RN1.2, X17.4
unnamed: PDN23:RN2.8, X17.5
unnamed: PDN23:RN2.6, X17.6
unnamed: PDN23:RN2.4, X17.7
unnamed: PDN23:RN2.2, X17.8
unnamed: PDN24:RN1.8, X17.9
unnamed: PDN24:RN1.6, X17.10
unnamed: PDN24:RN1.4, X17.11
unnamed: PDN24:RN1.2, X17.12
unnamed: PDN24:RN2.8, X17.13
unnamed: PDN24:RN2.6, X17.14
unnamed: PDN24:RN2.4, X17.15
unnamed: PDN24:RN2.2, X17.16
unnamed: PDN25:RN1.8, X17.17
unnamed: PDN25:RN1.6, X17.18
unnamed: PDN25:RN1.4, X17.19
unnamed: PDN25:RN1.2, X17.20
unnamed: PDN25:RN2.8, X17.21
unnamed: PDN25:RN2.6, X17.22
unnamed: PDN25:RN2.4, X17.23
unnamed: PDN25:RN2.2, X17.24
unnamed: PDN26:RN1.8, X17.25
unnamed: PDN26:RN1.6, X17.26
unnamed: PDN26:RN1.4, X17.27
unnamed: PDN26:RN1.2, X17.28
unnamed: PDN26:RN2.8, X17.29
unnamed: PDN26:RN2.6, X17.30
unnamed: PDN26:RN2.4, X17.31
unnamed: PDN26:RN2.2, X17.32
unnamed: PDN27:RN1.8, X17.33
unnamed: PDN27:RN1.6, X17.34
unnamed: PDN27:RN1.4, X17.35
unnamed: PDN27:RN1.2, X17.36
unnamed: PDN27:RN2.8, X17.37
unnamed: PDN27:RN2.6, X17.38
unnamed: PDN27:RN2.4, X17.39
unnamed: PDN27:RN2.2, X17.40
unnamed: PDN28:RN1.8, X19.1
unnamed: PDN28:RN1.6, X19.2
unnamed: PDN28:RN1.4, X19.3
unnamed: PDN28:RN1.2, X19.4
unnamed: PDN28:RN2.8, X19.5
unnamed: PDN28:RN2.6, X19.6
unnamed: PDN28:RN2.4, X19.7
unnamed: PDN28:RN2.2, X19.8
unnamed: PDN29:RN1.8, X19.9
unnamed: PDN29:RN1.6, X19.10
unnamed: PDN29:RN1.4, X19.11
unnamed: PDN29:RN1.2, X19.12
unnamed: PDN29:RN2.8, X19.13
unnamed: PDN29:RN2.6, X19.14
unnamed: PDN29:RN2.4, X19.15
unnamed: PDN29:RN2.2, X19.16
unnamed: PDN30:RN1.8, X19.17
unnamed: PDN30:RN1.6, X19.18
unnamed: PDN30:RN1.4, X19.19
unnamed: PDN30:RN1.2, X19.20
unnamed: PDN30:RN2.8, X19.21
unnamed: PDN30:RN2.6, X19.22
unnamed: PDN30:RN2.4, X19.23
unnamed: PDN30:RN2.2, X19.24
unnamed: PDN31:RN1.8, X19.25
unnamed: PDN31:RN1.6, X19.26
unnamed: PDN31:RN1.4, X19.27
unnamed: PDN31:RN1.2, X19.28
unnamed: PDN31:RN2.8, X19.29
unnamed: PDN31:RN2.6, X19.30
unnamed: PDN31:RN2.4, X19.31
unnamed: PDN31:RN2.2, X19.32
unnamed: PDN32:RN1.8, X19.33
unnamed: PDN32:RN1.6, X19.34
unnamed: PDN32:RN1.4, X19.35
unnamed: PDN32:RN1.2, X19.36
unnamed: PDN32:RN2.8, X19.37
unnamed: PDN32:RN2.6, X19.38
unnamed: PDN32:RN2.4, X19.39
unnamed: PDN32:RN2.2, X19.40
unnamed: PDN33:RN1.8, X21.1
unnamed: PDN33:RN1.6, X21.2
unnamed: PDN33:RN1.4, X21.3
unnamed: PDN33:RN1.2, X21.4
unnamed: PDN34:RN1.8, X23.1
unnamed: PDN34:RN1.6, X23.2
unnamed: PDN34:RN1.4, X23.3
unnamed: PDN34:RN1.2, X23.4
unnamed: PDN34:RN2.8, X23.5
unnamed: PDN34:RN2.6, X23.6
unnamed: PDN34:RN2.4, X23.7
unnamed: PDN34:RN2.2, X23.8
unnamed: PDN35:RN1.8, X23.9
unnamed: PDN35:RN1.6, X23.10
unnamed: PDN35:RN1.4, X23.11
unnamed: PDN35:RN1.2, X23.12
unnamed: PDN35:RN2.8, X23.13
unnamed: PDN35:RN2.6, X23.14
unnamed: PDN35:RN2.4, X23.15
unnamed: PDN35:RN2.2, X23.16
unnamed: PDN36:RN1.8, X23.17
unnamed: PDN36:RN1.6, X23.18
unnamed: PDN36:RN1.4, X23.19
unnamed: PDN36:RN1.2, X23.20
unnamed: PDN36:RN2.8, X23.21
unnamed: PDN36:RN2.6, X23.22
unnamed: PDN36:RN2.4, X23.23
unnamed: PDN36:RN2.2, X23.24
unnamed: PDN37:RN1.8, X23.25
unnamed: PDN37:RN1.6, X23.26
unnamed: PDN37:RN1.4, X23.27
unnamed: PDN37:RN1.2, X23.28
unnamed: PDN37:RN2.8, X23.29
unnamed: PDN37:RN2.6, X23.30
unnamed: PDN37:RN2.4, X23.31
unnamed: PDN37:RN2.2, X23.32
unnamed: PDN38:RN1.8, X23.33
unnamed: PDN38:RN1.6, X23.34
unnamed: PDN38:RN1.4, X23.35
unnamed: PDN38:RN1.2, X23.36
unnamed: PDN38:RN2.8, X23.37
unnamed: PDN38:RN2.6, X23.38
unnamed: PDN38:RN2.4, X23.39
unnamed: PDN38:RN2.2, X23.40
unnamed: PDN39:RN1.8, X25.1
unnamed: PDN39:RN1.6, X25.2
unnamed: PDN39:RN1.4, X25.3
unnamed: PDN39:RN1.2, X25.4
unnamed: PDN39:RN2.8, X25.5
unnamed: PDN39:RN2.6, X25.6
unnamed: PDN39:RN2.4, X25.7
unnamed: PDN39:RN2.2, X25.8
unnamed: PDN40:RN1.8, X25.9
unnamed: PDN40:RN1.6, X25.10
unnamed: PDN40:RN1.4, X25.11
unnamed: PDN40:RN1.2, X25.12
unnamed: PDN40:RN2.8, X25.13
unnamed: PDN40:RN2.6, X25.14
unnamed: PDN40:RN2.4, X25.15
unnamed: PDN40:RN2.2, X25.16
unnamed: PDN41:RN1.8, X25.17
unnamed: PDN41:RN1.6, X25.18
unnamed: PDN41:RN1.4, X25.19
unnamed: PDN41:RN1.2, X25.20
unnamed: PDN41:RN2.8, X25.21
unnamed: PDN41:RN2.6, X25.22
unnamed: PDN41:RN2.4, X25.23
unnamed: PDN41:RN2.2, X25.24
unnamed: PDN42:RN1.8, X25.25
unnamed: PDN42:RN1.6, X25.26
unnamed: PDN42:RN1.4, X25.27
unnamed: PDN42:RN1.2, X25.28
unnamed: PDN42:RN2.8, X25.29
unnamed: PDN42:RN2.6, X25.30
unnamed: PDN42:RN2.4, X25.31
unnamed: PDN42:RN2.2, X25.32
unnamed: PDN43:RN1.8, X25.33
unnamed: PDN43:RN1.6, X25.34
unnamed: PDN43:RN1.4, X25.35
unnamed: PDN43:RN1.2, X25.36
unnamed: PDN43:RN2.8, X25.37
unnamed: PDN43:RN2.6, X25.38
unnamed: PDN43:RN2.4, X25.39
unnamed: PDN43:RN2.2, X25.40
unnamed: PDN44:RN1.8, X27.1
unnamed: PDN44:RN1.6, X27.2
unnamed: PDN44:RN1.4, X27.3
unnamed: PDN44:RN1.2, X27.4
unnamed: PDN45:RN1.8, X29.1
unnamed: PDN45:RN1.6, X29.2
unnamed: PDN45:RN1.4, X29.3
unnamed: PDN45:RN1.2, X29.4
unnamed: PDN45:RN2.8, X29.5
unnamed: PDN45:RN2.6, X29.6
unnamed: PDN45:RN2.4, X29.7
unnamed: PDN45:RN2.2, X29.8
unnamed: PDN46:RN1.8, X29.9
unnamed: PDN46:RN1.6, X29.10
unnamed: PDN46:RN1.4, X29.11
unnamed: PDN46:RN1.2, X29.12
unnamed: PDN46:RN2.8, X29.13
unnamed: PDN46:RN2.6, X29.14
unnamed: PDN46:RN2.4, X29.15
unnamed: PDN46:RN2.2, X29.16
unnamed: PDN47:RN1.8, X29.17
unnamed: PDN47:RN1.6, X29.18
unnamed: PDN47:RN1.4, X29.19
unnamed: PDN47:RN1.2, X29.20
unnamed: PDN47:RN2.8, X29.21
unnamed: PDN47:RN2.6, X29.22
unnamed: PDN47:RN2.4, X29.23
unnamed: PDN47:RN2.2, X29.24
unnamed: PDN48:RN1.8, X29.25
unnamed: PDN48:RN1.6, X29.26
unnamed: PDN48:RN1.4, X29.27
unnamed: PDN48:RN1.2, X29.28
unnamed: PDN48:RN2.8, X29.29
unnamed: PDN48:RN2.6, X29.30
unnamed: PDN48:RN2.4, X29.31
unnamed: PDN48:RN2.2, X29.32
unnamed: PDN49:RN1.8, X29.33
unnamed: PDN49:RN1.6, X29.34
unnamed: PDN49:RN1.4, X29.35
unnamed: PDN49:RN1.2, X29.36
unnamed: PDN49:RN2.8, X29.37
unnamed: PDN49:RN2.6, X29.38
unnamed: PDN49:RN2.4, X29.39
unnamed: PDN49:RN2.2, X29.40
unnamed: PDN50:RN1.8, X31.1
unnamed: PDN50:RN1.6, X31.2
unnamed: PDN50:RN1.4, X31.3
unnamed: PDN50:RN1.2, X31.4
unnamed: PDN50:RN2.8, X31.5
unnamed: PDN50:RN2.6, X31.6
unnamed: PDN50:RN2.4, X31.7
unnamed: PDN50:RN2.2, X31.8
unnamed: PDN51:RN1.8, X31.9
unnamed: PDN51:RN1.6, X31.10
unnamed: PDN51:RN1.4, X31.11
unnamed: PDN51:RN1.2, X31.12
unnamed: PDN51:RN2.8, X31.13
unnamed: PDN51:RN2.6, X31.14
unnamed: PDN51:RN2.4, X31.15
unnamed: PDN51:RN2.2, X31.16
unnamed: PDN52:RN1.8, X31.17
unnamed: PDN52:RN1.6, X31.18
unnamed: PDN52:RN1.4, X31.19
unnamed: PDN52:RN1.2, X31.20
unnamed: PDN52:RN2.8, X31.21
unnamed: PDN52:RN2.6, X31.22
unnamed: PDN52:RN2.4, X31.23
unnamed: PDN52:RN2.2, X31.24
unnamed: PDN53:RN1.8, X31.25
unnamed: PDN53:RN1.6, X31.26
unnamed: PDN53:RN1.4, X31.27
unnamed: PDN53:RN1.2, X31.28
unnamed: PDN53:RN2.8, X31.29
unnamed: PDN53:RN2.6, X31.30
unnamed: PDN53:RN2.4, X31.31
unnamed: PDN53:RN2.2, X31.32
unnamed: PDN54:RN1.8, X31.33
unnamed: PDN54:RN1.6, X31.34
unnamed: PDN54:RN1.4, X31.35
unnamed: PDN54:RN1.2, X31.36
unnamed: PDN54:RN2.8, X31.37
unnamed: PDN54:RN2.6, X31.38
unnamed: PDN54:RN2.4, X31.39
unnamed: PDN54:RN2.2, X31.40
unnamed: PDN55:RN1.8, X33.1
unnamed: PDN55:RN1.6, X33.2
unnamed: PDN55:RN1.4, X33.3
unnamed: PDN55:RN1.2, X33.4
unnamed: PDN56:RN1.8, X35.1
unnamed: PDN56:RN1.6, X35.2
unnamed: PDN56:RN1.4, X35.3
unnamed: PDN56:RN1.2, X35.4
unnamed: PDN56:RN2.8, X35.5
unnamed: PDN56:RN2.6, X35.6
unnamed: PDN56:RN2.4, X35.7
unnamed: PDN56:RN2.2, X35.8
unnamed: PDN57:RN1.8, X35.9
unnamed: PDN57:RN1.6, X35.10
unnamed: PDN57:RN1.4, X35.11
unnamed: PDN57:RN1.2, X35.12
unnamed: PDN57:RN2.8, X35.13
unnamed: PDN57:RN2.6, X35.14
unnamed: PDN57:RN2.4, X35.15
unnamed: PDN57:RN2.2, X35.16
unnamed: PDN58:RN1.8, X35.17
unnamed: PDN58:RN1.6, X35.18
unnamed: PDN58:RN1.4, X35.19
unnamed: PDN58:RN1.2, X35.20
unnamed: PDN58:RN2.8, X35.21
unnamed: PDN58:RN2.6, X35.22
unnamed: PDN58:RN2.4, X35.23
unnamed: PDN58:RN2.2, X35.24
unnamed: PDN59:RN1.8, X35.25
unnamed: PDN59:RN1.6, X35.26
unnamed: PDN59:RN1.4, X35.27
unnamed: PDN59:RN1.2, X35.28
unnamed: PDN59:RN2.8, X35.29
unnamed: PDN59:RN2.6, X35.30
unnamed: PDN59:RN2.4, X35.31
unnamed: PDN59:RN2.2, X35.32
unnamed: PDN60:RN1.8, X35.33
unnamed: PDN60:RN1.6, X35.34
unnamed: PDN60:RN1.4, X35.35
unnamed: PDN60:RN1.2, X35.36
unnamed: PDN60:RN2.8, X35.37
unnamed: PDN60:RN2.6, X35.38
unnamed: PDN60:RN2.4, X35.39
unnamed: PDN60:RN2.2, X35.40
unnamed: PDN61:RN1.8, X37.1
unnamed: PDN61:RN1.6, X37.2
unnamed: PDN61:RN1.4, X37.3
unnamed: PDN61:RN1.2, X37.4
unnamed: PDN61:RN2.8, X37.5
unnamed: PDN61:RN2.6, X37.6
unnamed: PDN61:RN2.4, X37.7
unnamed: PDN61:RN2.2, X37.8
unnamed: PDN62:RN1.8, X37.9
unnamed: PDN62:RN1.6, X37.10
unnamed: PDN62:RN1.4, X37.11
unnamed: PDN62:RN1.2, X37.12
unnamed: PDN62:RN2.8, X37.13
unnamed: PDN62:RN2.6, X37.14
unnamed: PDN62:RN2.4, X37.15
unnamed: PDN62:RN2.2, X37.16
unnamed: PDN63:RN1.8, X37.17
unnamed: PDN63:RN1.6, X37.18
unnamed: PDN63:RN1.4, X37.19
unnamed: PDN63:RN1.2, X37.20
unnamed: PDN63:RN2.8, X37.21
unnamed: PDN63:RN2.6, X37.22
unnamed: PDN63:RN2.4, X37.23
unnamed: PDN63:RN2.2, X37.24
unnamed: PDN64:RN1.8, X37.25
unnamed: PDN64:RN1.6, X37.26
unnamed: PDN64:RN1.4, X37.27
unnamed: PDN64:RN1.2, X37.28
unnamed: PDN64:RN2.8, X37.29
unnamed: PDN64:RN2.6, X37.30
unnamed: PDN64:RN2.4, X37.31
unnamed: PDN64:RN2.2, X37.32
unnamed: PDN65:RN1.8, X37.33
unnamed: PDN65:RN1.6, X37.34
unnamed: PDN65:RN1.4, X37.35
unnamed: PDN65:RN1.2, X37.36
unnamed: PDN65:RN2.8, X37.37
unnamed: PDN65:RN2.6, X37.38
unnamed: PDN65:RN2.4, X37.39
unnamed: PDN65:RN2.2, X37.40
unnamed: PDN66:RN1.8, X39.1
unnamed: PDN66:RN1.6, X39.2
unnamed: PDN66:RN1.4, X39.3
unnamed: PDN66:RN1.2, X39.4
unnamed: PDN67:RN1.8, X41.1
unnamed: PDN67:RN1.6, X41.2
unnamed: PDN67:RN1.4, X41.3
unnamed: PDN67:RN1.2, X41.4
unnamed: PDN67:RN2.8, X41.5
unnamed: PDN67:RN2.6, X41.6
unnamed: PDN67:RN2.4, X41.7
unnamed: PDN67:RN2.2, X41.8
unnamed: PDN68:RN1.8, X41.9
unnamed: PDN68:RN1.6, X41.10
unnamed: PDN68:RN1.4, X41.11
unnamed: PDN68:RN1.2, X41.12
unnamed: PDN68:RN2.8, X41.13
unnamed: PDN68:RN2.6, X41.14
unnamed: PDN68:RN2.4, X41.15
unnamed: PDN68:RN2.2, X41.16
unnamed: PDN69:RN1.8, X41.17
unnamed: PDN69:RN1.6, X41.18
unnamed: PDN69:RN1.4, X41.19
unnamed: PDN69:RN1.2, X41.20
unnamed: PDN69:RN2.8, X41.21
unnamed: PDN69:RN2.6, X41.22
unnamed: PDN69:RN2.4, X41.23
unnamed: PDN69:RN2.2, X41.24
unnamed: PDN70:RN1.8, X41.25
unnamed: PDN70:RN1.6, X41.26
unnamed: PDN70:RN1.4, X41.27
unnamed: PDN70:RN1.2, X41.28
unnamed: PDN70:RN2.8, X41.29
unnamed: PDN70:RN2.6, X41.30
unnamed: PDN70:RN2.4, X41.31
unnamed: PDN70:RN2.2, X41.32
unnamed: PDN71:RN1.8, X41.33
unnamed: PDN71:RN1.6, X41.34
unnamed: PDN71:RN1.4, X41.35
unnamed: PDN71:RN1.2, X41.36
unnamed: PDN71:RN2.8, X41.37
unnamed: PDN71:RN2.6, X41.38
unnamed: PDN71:RN2.4, X41.39
unnamed: PDN71:RN2.2, X41.40
unnamed: PDN72:RN1.8, X43.1
unnamed: PDN72:RN1.6, X43.2
unnamed: PDN72:RN1.4, X43.3
unnamed: PDN72:RN1.2, X43.4
unnamed: PDN72:RN2.8, X43.5
unnamed: PDN72:RN2.6, X43.6
unnamed: PDN72:RN2.4, X43.7
unnamed: PDN72:RN2.2, X43.8
unnamed: PDN73:RN1.8, X43.9
unnamed: PDN73:RN1.6, X43.10
unnamed: PDN73:RN1.4, X43.11
unnamed: PDN73:RN1.2, X43.12
unnamed: PDN73:RN2.8, X43.13
unnamed: PDN73:RN2.6, X43.14
unnamed: PDN73:RN2.4, X43.15
unnamed: PDN73:RN2.2, X43.16
unnamed: PDN74:RN1.8, X43.17
unnamed: PDN74:RN1.6, X43.18
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
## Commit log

2016-01-22 First Commit
    The Arduino_ATMega folder contains all of the files given to us for
    this assignment to program the board. This commit also contains
    Lab2/program.c which is what we have as far as parts 0 and 1 of Lab2.
    This probably doesn’t work because of the source files in the makefile
    don’t reference the correct file… yet.
2016-01-26 File Structure Updates
    Makefile and importing now works with the setup directories.
2016-01-27 Seven Segment
    The seven segment display works when pins 3 or 8 are plugged into high
    voltage and the corresponding functions’ pins are plugged into pins 1,
    6, and 9. The code compiles and successfully displays the segment.
2016-01-27 Part 4
    working on part 4
2016-01-28 More Stuff
    End of working on Wednesday.
2016-01-28 Lab 3 Part 0
    Lab 3 part 0 is done. Makefile is setup to run Lab 3’s program.c
2016-01-28 Lab 3: Part 2
    We just finished Lab 3 Part 2, and we’re done for today. (Thursday
    1/28).
2016-02-02 Tutorial
    Shoddy Making the stepper motor step.
2016-02-02 Finished Step
    Finished the step motor file.
2016-02-09 Part3
    Working on Part 3
2016-02-09 Part 3
    Finished Part 3
2016-02-11 Part 5
    Working on stuff
2016-02-11 Part 5
    Updates to stuff
2016-02-11 Part 5
    This code now accurately puts a character into the console when it is
    pressed. It also puts the correct frequency waveform for pressing
    different columns.
2016-02-11 Lab 3
    Finished Lab 3, and made lab 4 folder.
2016-02-16 Tutorial 2
    Tutorial 2 started
2016-02-16 Updated Makefile
    Changed device for Sahithya’s computer
2016-02-16 Lab 4
    Working towards Lab 4
2016-02-17 Working Towards Working
    Next time, try polling to generate the output.
2016-02-18 PART 1
    Part 1 is working!!! WOOOO!
2016-02-18 Part 3 finished
    Part 3 is finished and working.
2016-02-23 Finalize Lab 4
    Finished up Lab 4.
2016-02-23 Download Files
    Added the framework given in the lab.
2016-02-24 Channel Update
    Update the channel to channel 16.
2016-03-25 makefile & output
    The makefile and output have changed for the ATMega
2016-03-25 New Folder
2016-03-25 Stacks Worksheet
    Recurse function for one of the 350 labs
2016-03-25 Deleted File
2016-03-27 Created a test file to make a new folder
2016-03-27 Added files for the 3 parts for laser cutting
2016-03-28 SolidWorks
    Made a new folder for all the SolidWorks files. Also, recreated the
    files from scratch in cm to make sure they’re correct.
2016-03-28 DWG
    Adding DWG files for the solid works parts.
2016-04-08 Create ArduinoCode
    Arduino code for testing of one column
2016-04-08 Rearranging
    Rearranged and put makefile stuff in for the Atmega micro controller
2016-04-09 Incremental Updates
    Fixed quite a few errors and made things quicker/more reliable. It’s
    still not working, but it’s closer.
2016-04-10 IT WORKS
    IT WORKS
2016-04-11 Eagle Documents
    Schematic upload
2016-04-12 Socket Work
    Werk Werk Werk
2016-04-12 Finished Schematic
    Finished hooking up the pins to the rest of the board in the schematic
    and made a board. Didn’t place elements on the board, yet.
2016-04-13 Schematic Updates
    Updated Schematic with modules. The schematic is now larger, and we’re
    planning on having a single PCB over the back of the container.
2016-04-13 More Schematic Updates
2016-04-18 Arduino From MODLAB
    Dragged in the file from the arduino library that ModLab uses.
2016-04-18 File Restructuring
2016-04-19 Atmega Compile Works
    The code for the atmega works in theory. We don’t have a board to test
    it with yet, but the code compiles.
2016-04-19 Updating Files
2016-04-19 Updating UART.h
2016-04-20 Back to the Uno
    We went back to the Uno because the Leonardo was giving us too much
    trouble for serial output and watching the code run.
2016-04-20 Output update
2016-04-20 Library for LCD Screen
    I added the library for the LCD screen to my personal directory, and
    you should, too, but I needed to add it to gitignore because I can’t
    commit a copy of the other project.
2016-04-21 Makefiles oh makefiles
    Working on the makefiles for the project.
2016-04-21 It compiles!
2016-04-21 LCD Files
2016-04-21 Cleaning Files
    Cleaned up a lot of useless files from the project.
2016-04-22 Making Header Files
2016-04-22 Header Files
    Updating header files
2016-04-22 Making Main.c work
    Been working with main.c to get things working.
2016-04-22 WORKING
    This is the working version of the code so far. What isn’t working is
    the voltage level and water level. That will be fixed soon.
2016-04-23 Updating .c Files
    Updated the .c files for Sensor and Display. Also made a .c for
    storage, but haven’t really done much with it.
2016-04-23 Make Again
    Re made the project and saves more things.
2016-04-23 padding in display
    updated the padding var
2016-04-23 Deleted .lst and .o files
2016-04-23 changing the gitignore
2016-04-23 Changing the gitignore again
    making it not .ihex, .d, .lst
2016-04-24 Edited storage.c and storage.h files
2016-04-24 Working on Display and Main.c
    The display.c has more stuff in it.
2016-04-25 Display Code
    I added some tweaks to the display code including making the total
    output work. The hourly output should work as well when it is set.
2016-04-25 Fixed sizeof in display.c
2016-04-25 Demo Day 1
    Updated the info for demo day 1, commenting out stuff that isn’t going
    to be displayed.
2016-05-01 Storage.h
    Changing the header file to store and retrieve more appropriate data.
2016-05-01 Working on Display and Storage
2016-05-01 Updating
    Updating Storage.h to contain some more info
2016-05-01 Making it make
2016-05-01 Updating Display Code
2016-05-01 working on main.c
    I made the variables have better names.
2016-05-01 Updated storage.c and storage.h
2016-05-01 main and storage work
2016-05-02 Fixed storage.h and storage.c
    Code works!
2016-05-03 Feedback
    Making a feedback loop for the data collection.

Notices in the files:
parts and their libraries:
SparkFun-AnalogIC: Licensing:Creative Commons ShareAlike 4.0 International - https://creativecommons.org/licenses/by-sa/4.0
